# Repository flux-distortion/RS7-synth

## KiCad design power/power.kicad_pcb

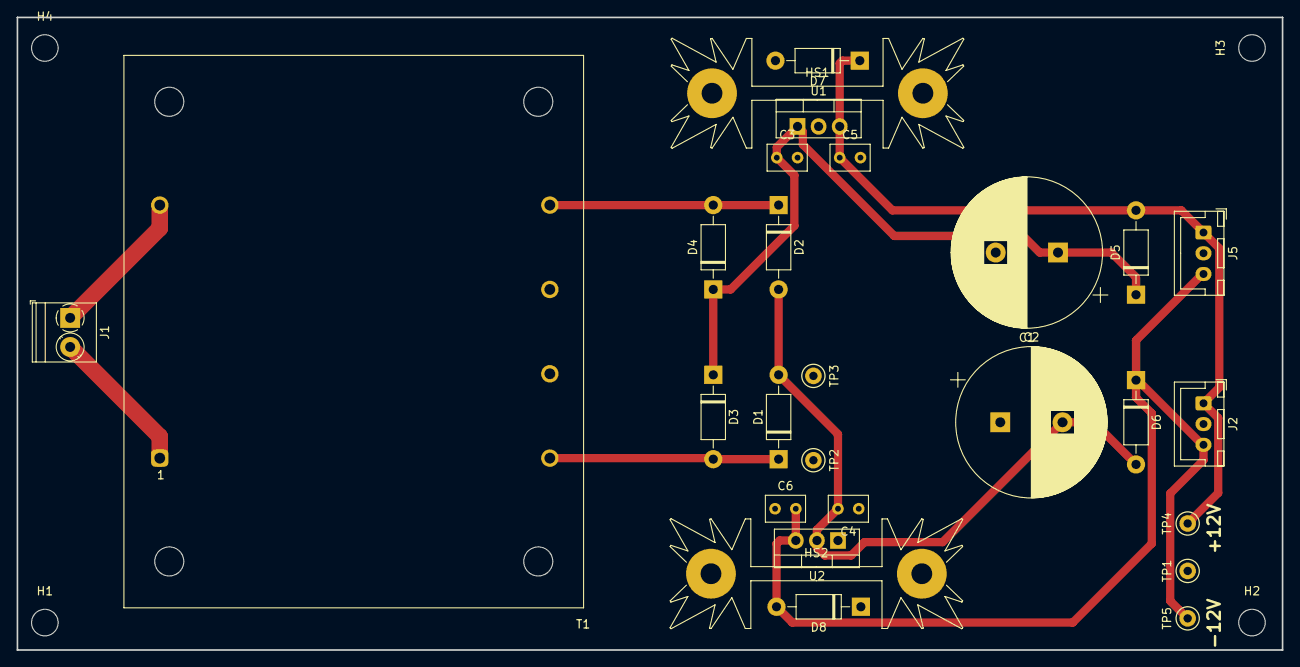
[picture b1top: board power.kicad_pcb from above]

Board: 2 copper layers, 152.4 x 76.2 mm, 31 parts (0 on the bottom side), 9 nets.

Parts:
C1, C2: 1000u; CP_Radial_D18.0mm_P7.50mm
C3, C4: 2.2u; C_Rect_L4.6mm_W3.0mm_P2.50mm_MKS02_FKP02
C5, C6: 1u; C_Rect_L4.6mm_W3.0mm_P2.50mm_MKS02_FKP02
D1, D2, D3, D4, D5, D6, D7, D8: 1N4002; D_DO-41_SOD81_P10.16mm_Horizontal
H1, H2, H3, H4: MountingHole; MountingHole_3.2mm_M3_DIN965
HS1, HS2: Heatsink; Heatsink_Fischer_SK104-STC-STIC_35x13mm_2xDrill2.5mm
J1: Screw_Terminal_01x02; TerminalBlock_Phoenix_PT-1,5-2-3.5-H_1x02_P3.50mm_Horizontal
J2, J5: Conn_01x03; JST_XH_B3B-XH-A_1x03_P2.50mm_Vertical
T1: Transformer_1P_2S_PCB; TRANSFORMER_Signal_ST-7-24
TP1, TP2, TP3, TP4, TP5: TestPoint; TestPoint_Keystone_5000-5004_Miniature
U1: LM7812_TO220; TO-220-3_Vertical
U2: LM7912_TO220; TO-220-3_Vertical

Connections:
+12V: C5.1, D5.2, D7.1, J2.1, J5.1, TP4.1, U1.3
-12V: C6.2, D6.1, D8.2, J2.3, J5.3, TP5.1, U2.3
/+12V_VI: C1.1, C3.1, D3.1, D4.1, D5.1, U1.1
/-12V_VI: C2.2, C4.2, D1.2, D2.2, D6.2, TP3.1, U2.2
GND: C1.2, C2.1, C3.2, C4.1, C5.2, C6.1, D7.2, D8.1, J2.2, J5.2, T1.6, T1.7, TP1.1, U1.2, U2.1
unnamed: D1.1, D3.2, T1.5, TP2.1
unnamed: D2.1, D4.2, T1.8
unnamed: J1.1, T1.4
unnamed: J1.2, T1.1

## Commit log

2019-10-18 added pdf schematic
